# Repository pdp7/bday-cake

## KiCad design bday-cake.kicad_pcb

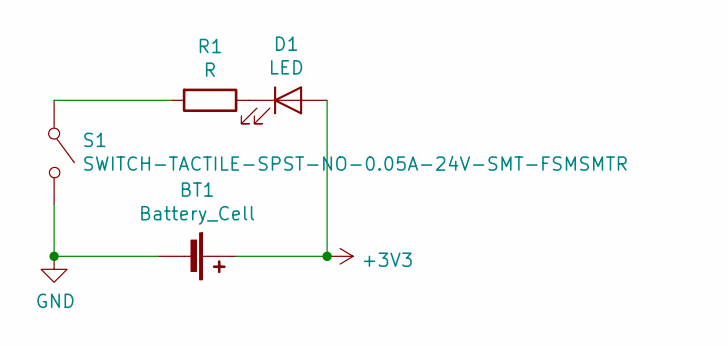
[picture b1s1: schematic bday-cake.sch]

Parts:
BT1: Battery_Cell; BatteryHolder_Keystone_3002_1x2032
D1: LED; LED_D5.0mm
R1: R; R_Axial_DIN0207_L6.3mm_D2.5mm_P7.62mm_Horizontal
S1: SWITCH-TACTILE-SPST-NO-0.05A-24V-SMT-FSMSMTR; SWITCH-ESWITCH-SLIDE-TH-EG1218

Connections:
+3V3: BT1.1 (+), D1.2 (A)
GND: BT1.2 (-), S1.2
unnamed: D1.1 (K), R1.1
unnamed: R1.2, S1.1

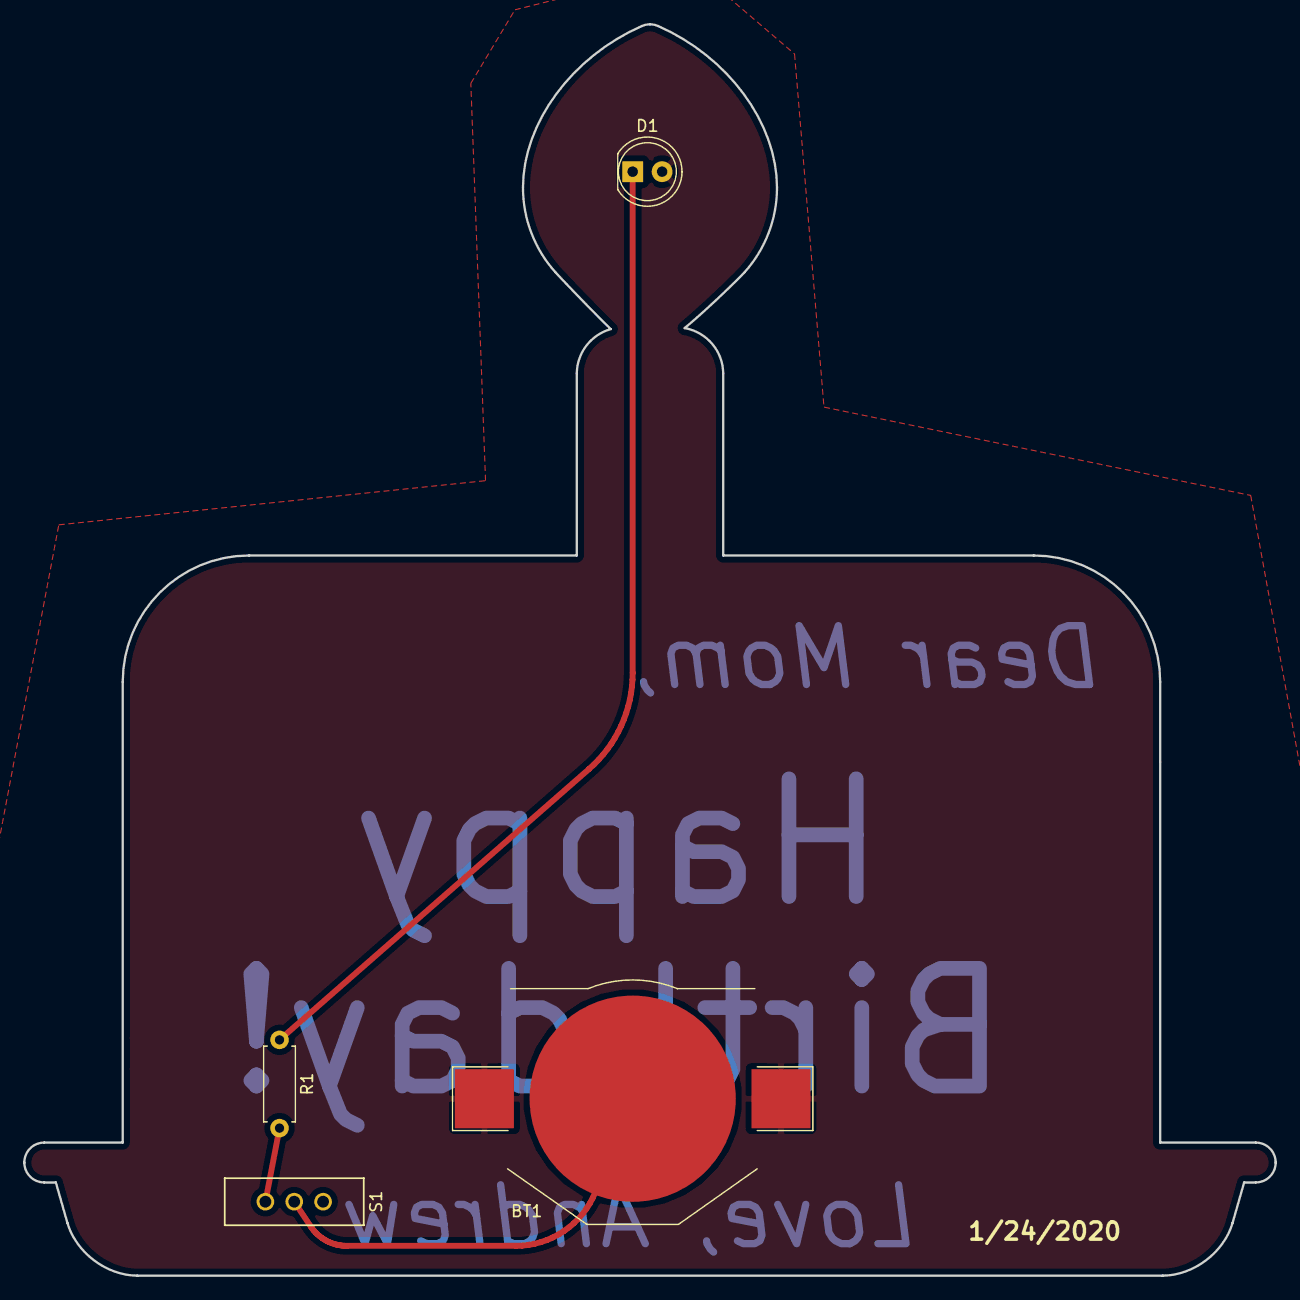
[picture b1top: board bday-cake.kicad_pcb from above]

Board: 2 copper layers, 108.0 x 108.0 mm, 4 parts (0 on the bottom side), 4 nets.

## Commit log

2020-01-20 update layout
2020-01-20 update schematic and layout
2020-01-25 add svg files for the cake outline
